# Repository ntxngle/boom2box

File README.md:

# boom2box
## What and Why

A driver that adapts LF signals from music to LRAs mounted on headphones to enhance felt bass experience. It does this with a bunch of QoL features like leds, neopixel, switches, audio jack for lantency free experience.

In addition, the LRAs can be mounted to not only headphones: shaking a table or chair can also produce excellent results.

This is to replicate the feeling of having high power speakers which I can neither afford nor run. I always enjoy bass in music, and this project should hopefully replicate this experience at minimal cost (and minimal noise to peers). A few years ago a friend showed me his headphones and I was surprised to feel that they shook like crazy. This same geek blasted shadow money wizard gang at the crisp 6AM on the bus, so I figure he must know his music. Fast forward to a few months ago, I put some terribly old desktop speakers on my desk and spent very valuable time (in lieu of studying for linear: I now have an F) on maximizing bass output. Obviously to my disappointment I didn't feel the chest thumping explosions found only in brazilian car modifier demonstrations, it did vibrate my desk a little in the right conditions. A suprisingingly bass-like experience. Thus, after finishing my other fallout project, I set out to replicate that feeling in the most intense way. While i couldn't mount double digit diameter subwoofers in my obviously homework filled drawers, I figured I could cheat by generating the vibrations directly.

## Tuff photos

Since the project isn't tuff I don't have tuff photos. Here are some unrelated photos.

## How it works
A DSP grabs low end of incoming audio, does some normalization (or not) and sends waveform to LRA driver.

These LRA drivers are the jewel of the project: automatic f_0 tracking, closed loop, etc etc read the zine. They are the ones responsible for driving the huge 15$ 3.5G thumpers that I plan to connect to them: another versatility of this project is that other LRAs work. Anything from 10mm aliexpress buzzers to massive rectangular theater grade shakers (3Vrms, 1/2 amp max) will work identically (other than f0: DSP should be retuned to pitch bass up or down closer to f0 for maximum amplitude.

To avoid delay between audio and motion, a headphone jack is included. This way I can control audio out to motion, to solve potential (and variable) desyncs. It also makes for a great way to turn wired over-ears (the target of this project) into wireless skull shakers.

## BOM
|name           |quantity|cost |link                                                                        |
|---------------|--------|-----|----------------------------------------------------------------------------|
|PCB            |1       |76.32|gerbers in this repo                                                        |
|LRA VG2230001H |2       |15.66|https://www.digikey.com/en/products/detail/vybronics-inc/VG2230001H/16719289|
|1c LiPo >500mAh|1       |5    |tear one out of genuinely anything                                          |
|Case           |1       |~2   |Simple ahh 3d printed case costs like 10 cents in filament                  |
|total          |1       |98.98| |

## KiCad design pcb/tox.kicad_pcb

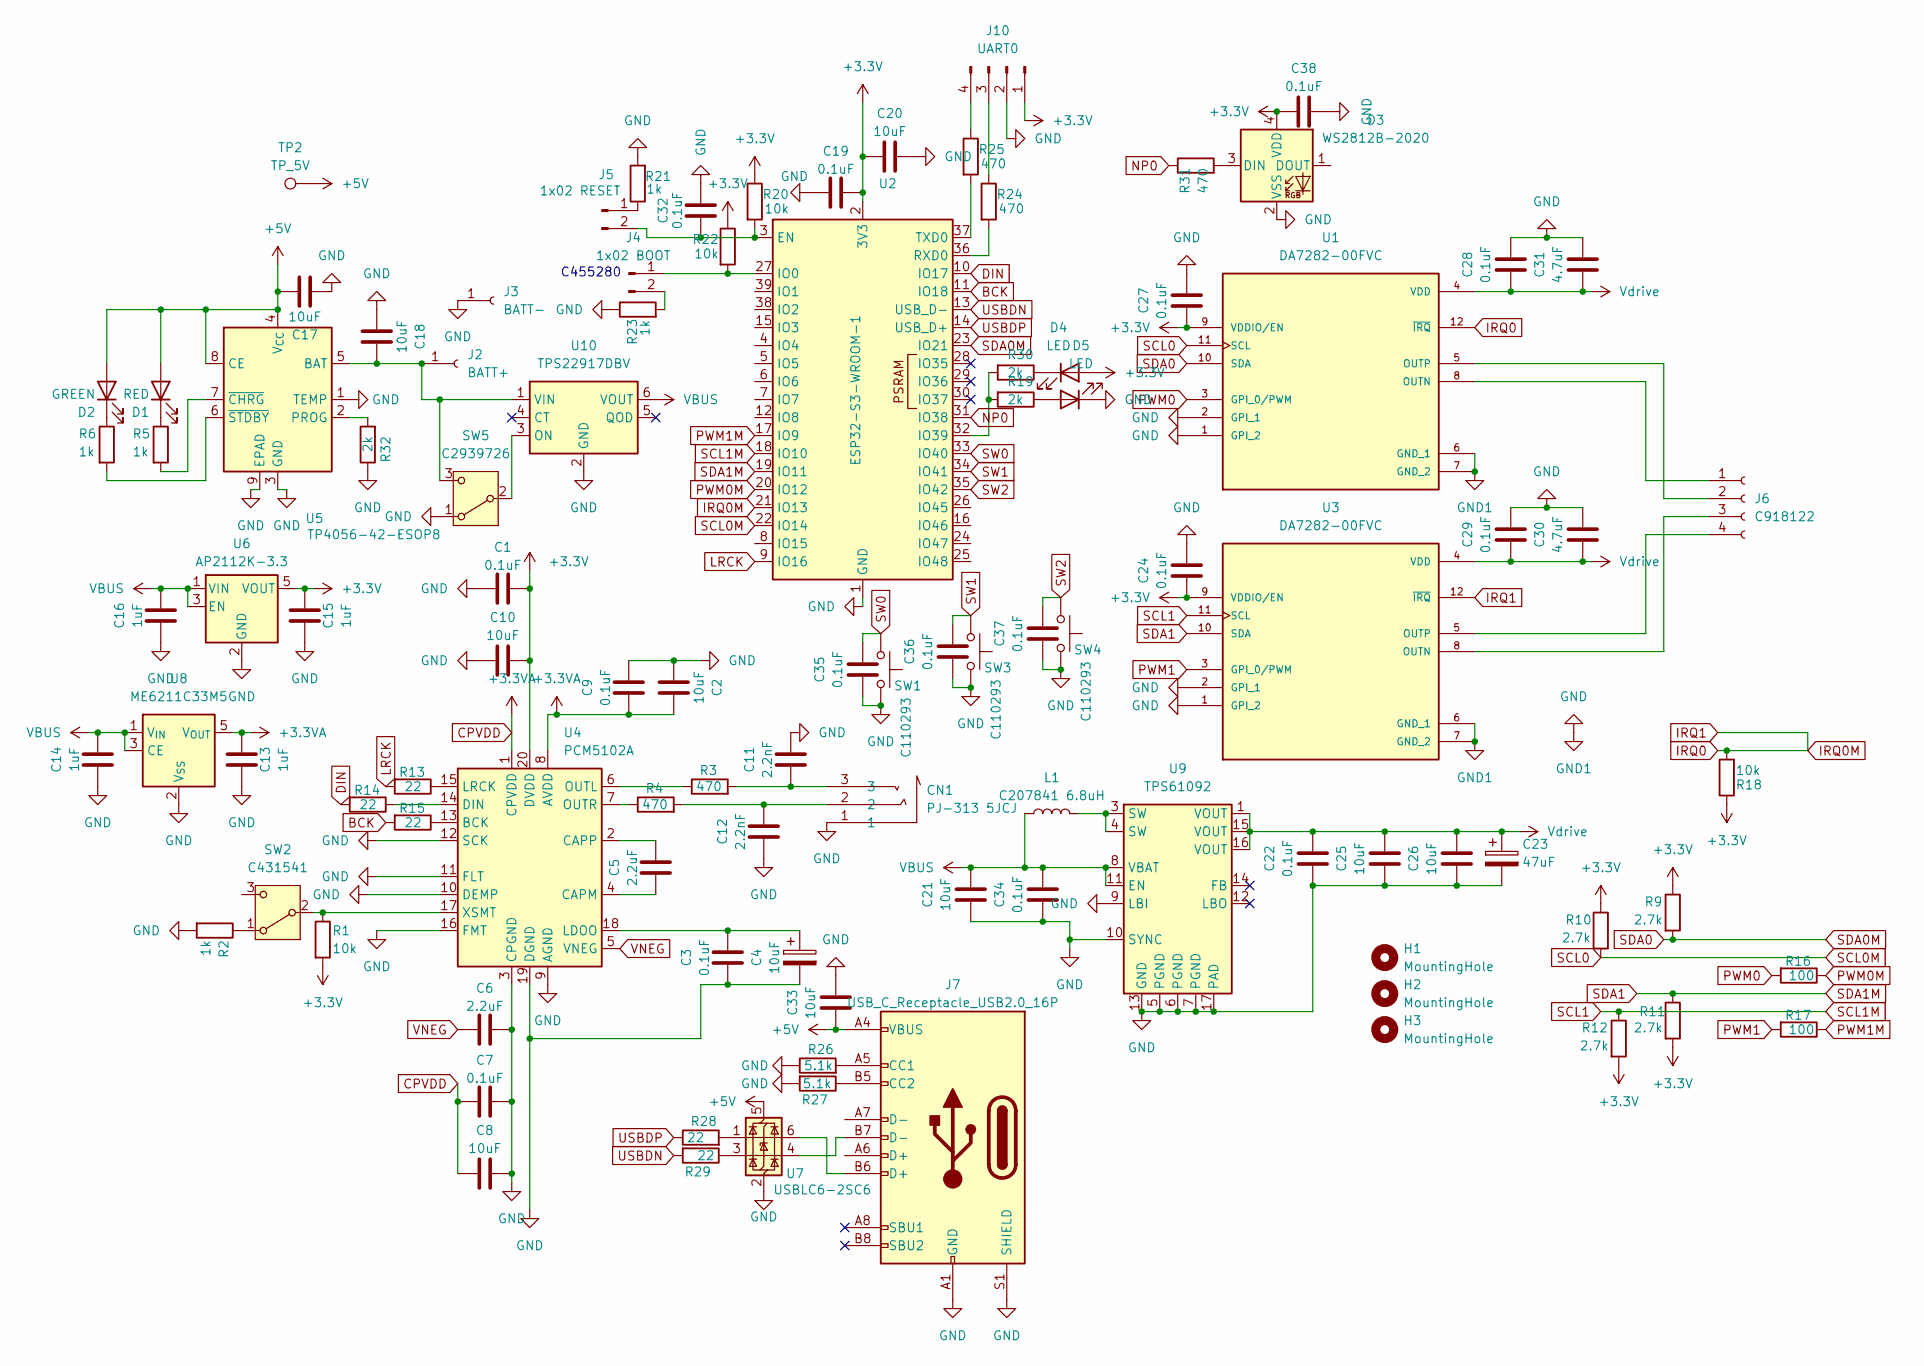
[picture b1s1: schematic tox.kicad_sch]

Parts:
C1, C3, C7, C9, C19, C22, C24, C27, C28, C29, C32, C34, C35, C36, C37, C38: 0.1uF; C_0603_1608Metric
C2, C4, C8, C10, C17, C18, C20, C21, C33: 10uF; C_0603_1608Metric
C5, C6: 2.2uF; C_0603_1608Metric
C11, C12: 2.2nF; C_0603_1608Metric
C13, C14, C15, C16: 1uF; C_0603_1608Metric
C23: 47uF; CP_EIA-3528-12_Kemet-T
C25, C26: 10uF; CP_EIA-3216-18_Kemet-A
C30, C31: 4.7uF; C_0603_1608Metric
CN1: PJ-313 5JCJ; AUDIO-TH_PJ-313_5JCJ; MPN PJ-313 5JCJ; LCSC Part C668607
D1: RED; LED_0603_1608Metric
D2: GREEN; LED_0603_1608Metric
D3: WS2812B-2020; LED_WS2812B-2020_PLCC4_2.0x2.0mm
D4, D5: LED; LED_0603_1608Metric
H1, H2, H3: MountingHole; MountingHole_2.1mm
J2: BATT+; TestPoint_THTPad_2.5x2.5mm_Drill1.2mm
J3: BATT-; TestPoint_THTPad_2.5x2.5mm_Drill1.2mm
J4: 1x02 BOOT; SW_Push_SPST_NO_Alps_SKRK
J5: 1x02 RESET; SW_Push_SPST_NO_Alps_SKRK
J6: C918122; CONN-TH_DB125-2.54-4P-GN
J7: USB_C_Receptacle_USB2.0_16P; USB_C_Receptacle_JAE_DX07S016JA1R1500
J10: UART0; PinHeader_1x04_P2.54mm_Vertical
L1: C207841 6.8uH; L_AVX_LMLP07A7
R1, R18, R20, R22: 10k; R_0603_1608Metric
R2, R5, R6, R21, R23: 1k; R_0603_1608Metric
R3, R4, R24, R25, R31: 470; R_0603_1608Metric
R9, R10, R11, R12: 2.7k; R_0603_1608Metric
R13, R14, R15, R28, R29: 22; R_0603_1608Metric
R16, R17: 100; R_0603_1608Metric
R19, R30, R32: 2k; R_0603_1608Metric
R26, R27: 5.1k; R_0603_1608Metric
SW1, SW3, SW4: C110293; SW_Push_1P1T-MP_NO_Horizontal_Alps_SKRTLAE010
SW2: C431541; SW_SPDT_PCM12
SW5: C2939726; SW_SS12D07VG4
TP2: TP_5V; TestPoint_Pad_D1.0mm
U1, U3: DA7282-00FVC; QFN-12-1EP_3x3mm_P0.5mm_EP1.45x1.45mm; PARTREV 3.1
U2: ESP32-S3-WROOM-1
U4: PCM5102A; TSSOP-20_4.4x6.5mm_P0.65mm
U5: TP4056-42-ESOP8; SOIC-8-1EP_3.9x4.9mm_P1.27mm_EP2.41x3.3mm
U6: AP2112K-3.3; SOT-23-5
U7: USBLC6-2SC6; SOT-23-6
U8: ME6211C33M5; SOT-23-5
U9: TPS61092; Texas_RSA_VQFN-16-1EP_4x4mm_P0.65mm_EP2.7x2.7mm
U10: TPS22917DBV; SOT-23-6

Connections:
+3.3V: C1.2, C10.1, C15.1, C19.2, C20.2, C24.2, C27.2, C38.2, D3.4 (VDD), D4.2 (A), J10.1, R1.2, R9.1, R10.1, R11.2, R12.2, R18.1, R20.1, R22.1, U1.9 (VDDIO/EN), U2.2 (3V3), U3.9 (VDDIO/EN), U4.20 (DVDD), U6.5 (VOUT)
+5V: C17.1, C33.2, D1.2 (A), D2.2 (A), J7.A4 (VBUS), J7.A9 (VBUS), J7.B4 (VBUS), J7.B9 (VBUS), TP2.1, U5.4 (V_{CC}), U5.8 (CE), U7.5 (VBUS)
BCK: R15.2, U2.11 (IO18)
CPVDD: C2.1, C7.1, C8.2, C9.1, C13.1, U4.1 (CPVDD), U4.8 (AVDD), U8.5 (V_{OUT})
DIN: R14.2, U2.10 (IO17)
GND: C1.1, C2.2, C3.1, C4.2, C6.2, C7.2, C8.1, C9.2, C10.2, C11.2, C12.1, C13.2, C14.1, C15.2, C16.1, C17.2, C18.2, C19.1, C20.1, C21.2, C22.2, C23.2, C24.1, C25.2, C26.2, C27.1, C28.1, C29.1, C30.1, C31.1, C32.2, C33.1, C34.2, C35.2, C36.2, C37.2, C38.1, CN1.1, D3.2 (VSS), D5.1 (K), J3.1, J7.A1 (GND), J7.A12 (GND), J7.B1 (GND), J7.B12 (GND), J7.S1 (SHIELD), J10.2, R2.2, R21.2, R23.1, R26.1, R27.2, R32.1, SW1.2, SW3.2, SW4.2, SW5.1 (A), U1.1 (GPI_2), U1.2 (GPI_1), U1.6 (GND_1), U1.7 (GND_2), U2.1 (GND), U2.40 (GND), U2.41 (GND), U3.1 (GPI_2), U3.2 (GPI_1), U3.6 (GND_1), U3.7 (GND_2), U4.3 (CPGND), U4.9 (AGND), U4.10 (DEMP), U4.11 (FLT), U4.12 (SCK), U4.16 (FMT), U4.19 (DGND), U5.1 (TEMP), U5.3 (GND), U5.9 (EPAD), U6.2 (GND), U7.2 (GND), U8.2 (V_{SS}), U9.5 (PGND), U9.6 (PGND), U9.7 (PGND), U9.9 (LBI), U9.10 (SYNC), U9.13 (GND), U9.17 (PAD), U10.2 (GND); also elsewhere on the board
IRQ0: R18.2, U1.12 (~IRQ), U2.21 (IO13), U3.12 (~IRQ)
LRCK: R13.2, U2.9 (IO16)
NP0: R31.1, U2.31 (IO38)
unnamed: C11.1, CN1.3, R3.2
unnamed: C12.2, CN1.2, R4.2
unnamed: D1.1 (K), R5.1
unnamed: D2.1 (K), R6.1
unnamed: D3.3 (DIN), R31.2
unnamed: D4.1 (K), R30.1
unnamed: D5.2 (A), R19.1
unnamed 16: C18.1, J2.1, SW5.3 (C), U5.5 (BAT), U10.1 (VIN); also elsewhere on the board
unnamed: J4.1, R22.2, U2.27 (IO0)
unnamed: J4.2, R23.2
unnamed: J5.1, R21.1
unnamed: C32.1, J5.2, R20.2, U2.3 (EN)
unnamed: J6.1, U1.8 (OUTN)
unnamed: J6.2, U1.5 (OUTP)
unnamed: J6.3, U3.8 (OUTN)
unnamed: J6.4, U3.5 (OUTP)
unnamed: J7.A5 (CC1), R26.2
unnamed: J7.B5 (CC2), R27.1
unnamed: J7.B6 (D+), U7.6 (I/O1)
unnamed: J7.B7 (D-), U7.4 (I/O2)
unnamed: J10.3, R24.1
unnamed: J10.4, R25.1
unnamed: L1.2, U9.3 (SW), U9.4 (SW)
unnamed: R28.2, U7.1 (I/O1)
unnamed: R29.1, U7.3 (I/O2)
unnamed: R2.1, SW2.1 (A)
unnamed: R1.1, SW2.2 (B), U4.17 (XSMT)
unnamed: SW5.2 (B), U10.3 (ON)
unnamed: R19.2, R30.2, U2.32 (IO39)
unnamed: R24.2, U2.36 (RXD0)
unnamed: R25.2, U2.37 (TXD0)
unnamed: R15.1, U4.13 (BCK)
unnamed: C5.1, U4.4 (CAPM)
unnamed: C5.2, U4.2 (CAPP)
unnamed: R14.1, U4.14 (DIN)
unnamed: C3.2, C4.1, U4.18 (LDOO)
unnamed: R13.1, U4.15 (LRCK)
unnamed: R3.1, U4.6 (OUTL)
unnamed: R4.1, U4.7 (OUTR)
unnamed: R32.2, U5.2 (PROG)
unnamed: R5.2, U5.7 (~CHRG)
unnamed: R6.2, U5.6 (~STDBY)
PWM0: R16.2, U1.3 (GPI_0/PWM)
PWM0M: R16.1, U2.20 (IO12)
PWM1: R17.2, U3.3 (GPI_0/PWM)
PWM1M: R17.1, U2.17 (IO9)
SCL0: R10.2, U1.11 (SCL), U2.22 (IO14)
SCL1: R12.1, U2.18 (IO10), U3.11 (SCL)
SDA0: R9.2, U1.10 (SDA), U2.23 (IO21)
SDA1: R11.1, U2.19 (IO11), U3.10 (SDA)
SW0: C35.1, SW1.1, U2.33 (IO40)
SW1: C36.1, SW3.1, U2.34 (IO41)
SW2: C37.1, SW4.1, U2.35 (IO42)
USBDN: R29.2, U2.13 (USB_D-)
USBDP: R28.1, U2.14 (USB_D+)
VBUS: C14.2, C16.2, C21.1, C34.1, L1.1, U6.1 (VIN), U6.3 (EN), U8.1 (V_{IN}), U8.3 (CE), U9.8 (VBAT), U9.11 (EN), U10.6 (VOUT)
VNEG: C6.1, U4.5 (VNEG)
Vdrive: C22.1, C23.1, C25.1, C26.1, C28.2, C29.2, C30.2, C31.2, U1.4 (VDD), U3.4 (VDD), U9.1 (VOUT), U9.15 (VOUT), U9.16 (VOUT)

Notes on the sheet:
C455280

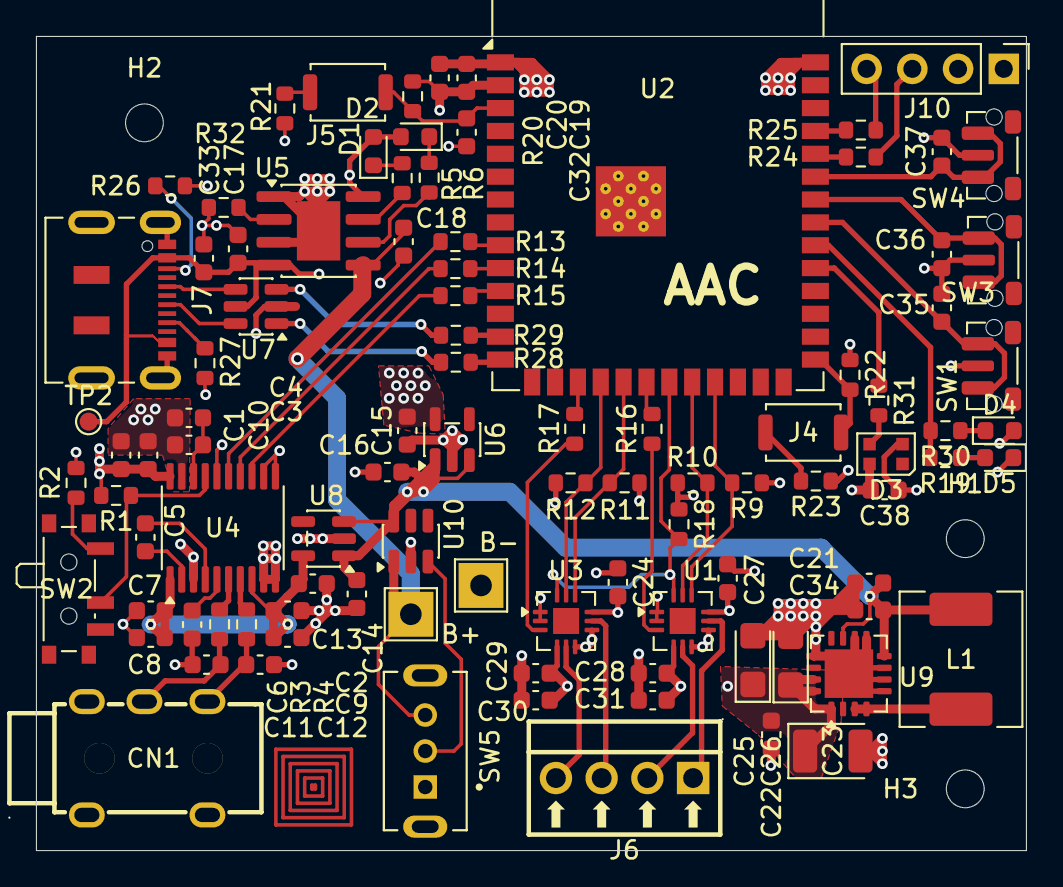
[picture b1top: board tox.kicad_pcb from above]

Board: 4 copper layers, 55.0 x 45.2 mm, 101 parts (0 on the bottom side), 67 nets.

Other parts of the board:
B+: BATT+; TestPoint_THTPad_2.5x2.5mm_Drill1.2mm
B-: BATT-; TestPoint_THTPad_2.5x2.5mm_Drill1.2mm

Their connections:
GND: B-.1; also elsewhere on the board
unnamed 16: B+.1; also elsewhere on the board

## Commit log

2026-06-18 larp
2026-06-18 l2larp
2026-06-18 bomlarp
2026-06-18 larpcad
    its taking a long time to upload so i will instead oh nvm its done
